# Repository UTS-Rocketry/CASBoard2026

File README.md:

# CAS Interface Board 2026

Control Actuation System (CAS) Interface Board for the UTS Rocketry avionics stack.

This board provides closed-loop control for the airbrake and roll control systems, along with sensor interfaces and onboard data logging. The design is based on the STM32F405RGT6 microcontroller and integrates inertial sensing, actuator control, and non-volatile storage.

The CAS board is intended to operate as part of the UTS Rocketry flight avionics architecture.

---

## Overview

The CAS Interface Board is responsible for:

- Airbrake deployment control
- Roll stabilization control
- Sensor acquisition
- Data logging
- Actuator interfacing

Closed-loop control is performed onboard using IMU and barometric sensor measurements.

---

## Hardware

### Microcontroller

STM32F405RGT6

- ARM Cortex-M4F
- 168 MHz
- Hardware floating point
- 1 MB Flash
- 192 KB RAM

---

### Sensors

#### IMU

LSM6DS3TR-C

Interface:

- SPI (4-wire)

Signals:

- SCK
- MOSI
- MISO
- CS
- DRDY Interrupt

Power:

- 3.3 V

---

#### Barometer

Interface:

- I2C

Signals:

- SCL
- SDA

Power:

- 3.3 V

---

### Storage

#### MicroSD Card

Interface:

- SPI

Signals:

- SCK
- MOSI
- MISO
- CS

Purpose:

- Flight data logging

---

#### External Flash

Interface:

- SPI

Purpose:

- Backup logging
- Blackbox storage

---

### Actuator Interfaces

#### Servo Outputs

- Airbrake Servo
- Roll Control Servo

Control Method:

- Timer PWM outputs

Power:

- Dedicated 5 V servo rail

Signal Voltage:

- 3.3 V logic

---

### Analog Inputs

#### Airbrake Position Feedback

External potentiometer input.

Signals:

- 3.3 V
- ADC Input
- GND

---

### Digital Inputs

#### Limit Switches

Digital inputs for actuator limits.

Typical configuration:

- External pull-down resistors
- GPIO input

---

#### IMU Interrupt

IMU data-ready interrupt.

Connected to STM32 EXTI input.

---

### Debug Interface

Serial Wire Debug (SWD)

Signals:

- SWDIO
- SWCLK
- NRST
- 3.3 V
- GND

Used for:

- Programming
- Debugging

---

## Communication Interfaces

### SPI Buses

SPI1

Used for:

- IMU

SPI2

Used for:

- MicroSD card
- External flash

---

### I2C Bus

I2C1

Used for:

- Barometer

---

## Power Architecture

### 3.3 V Rail

Supplies:

- MCU
- IMU
- Barometer
- Flash
- SD card logic

---

### 5 V Rail

Supplies:

- Servo motors

---

### Grounding

- Continuous ground plane
- Shared logic and servo ground

---

## Control System

### Airbrake Control

The CAS system predicts apogee using altitude and velocity estimates derived from sensor measurements.

Airbrake deployment is adjusted to reach the target apogee.

Inputs:

- Barometer altitude
- Estimated vertical velocity

Outputs:

- Airbrake servo PWM

---

### Roll Control

Roll stabilization is performed using gyroscope measurements from the IMU.

Inputs:

- Roll rate from IMU

Outputs:

- Roll control servo PWM

---

## Firmware

Development tools:

- STM32CubeMX
- STM32CubeIDE
- ST-Link

Features:

- SPI IMU driver
- I2C barometer driver
- PWM servo control
- SD card logging
- Flash logging
- Interrupt-driven sensor acquisition

---

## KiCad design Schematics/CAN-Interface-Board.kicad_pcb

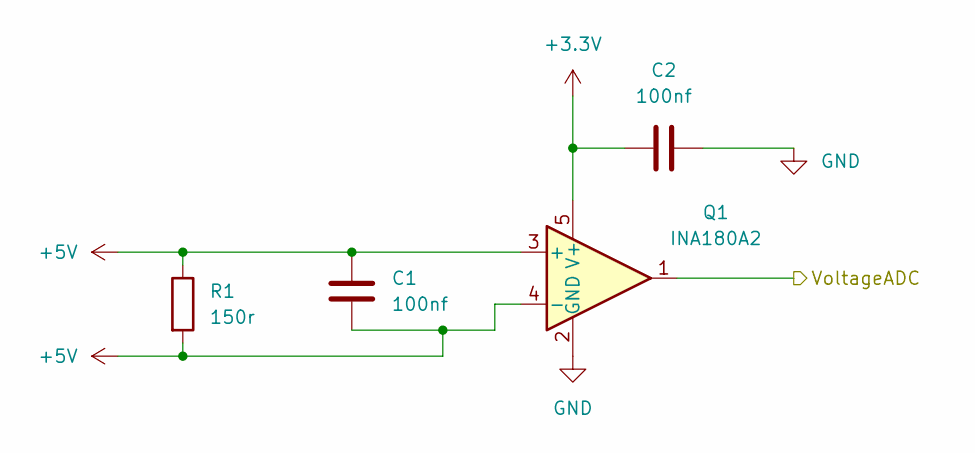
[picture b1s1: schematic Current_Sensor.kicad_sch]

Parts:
C1, C2: 100nf; C_0805_2012Metric_Pad1.18x1.45mm_HandSolder; LCSC Part C49678
Q1: INA180A2; SOT-23-5; LCSC Part C192764
R1: 150r; R_0805_2012Metric_Pad1.20x1.40mm_HandSolder; LCSC Part C4293416

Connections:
+3.3V: C2.1, Q1.5 (V+); also elsewhere on the board
+5V: C1.1, C1.2, Q1.3 (+), Q1.4 (-), R1.1, R1.2; also elsewhere on the board
/Current Sensor/VoltageADC: Q1.1; also elsewhere on the board
GND: C2.2, Q1.2 (GND); also elsewhere on the board

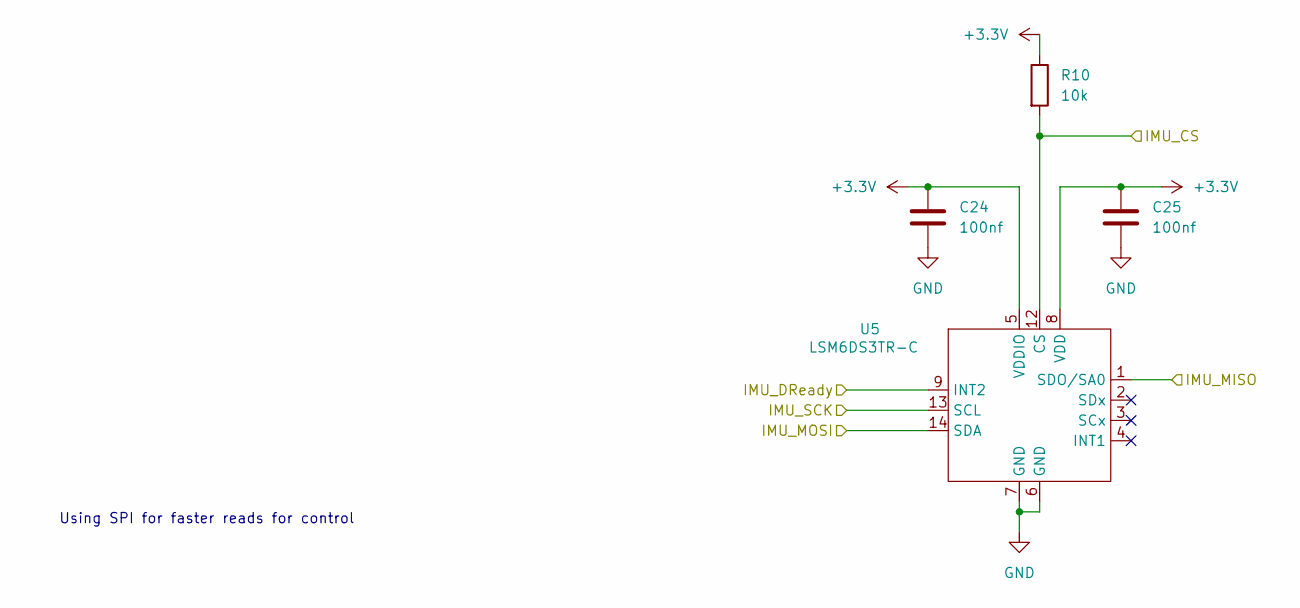
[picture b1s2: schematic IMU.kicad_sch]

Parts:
C24, C25: 100nf; C_0805_2012Metric_Pad1.18x1.45mm_HandSolder; LCSC Part C49678
R10: 10k; R_0805_2012Metric_Pad1.20x1.40mm_HandSolder; LCSC C84376
U5: LSM6DS3TR-C; LGA-14-2.5X3MM; LCSC Part C967633

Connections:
+3.3V: C24.1, C25.1, R10.1, U5.5 (VDDIO), U5.8 (VDD); also elsewhere on the board
/IMU/IMU_CS: R10.2, U5.12 (CS); also elsewhere on the board
/IMU/IMU_DReady: U5.9 (INT2); also elsewhere on the board
/IMU/IMU_MISO: U5.1 (SDO/SA0); also elsewhere on the board
/IMU/IMU_MOSI: U5.14 (SDA); also elsewhere on the board
/IMU/IMU_SCK: U5.13 (SCL); also elsewhere on the board
GND: C24.2, C25.2, U5.6 (GND), U5.7 (GND); also elsewhere on the board

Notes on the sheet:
Using SPI for faster reads for control

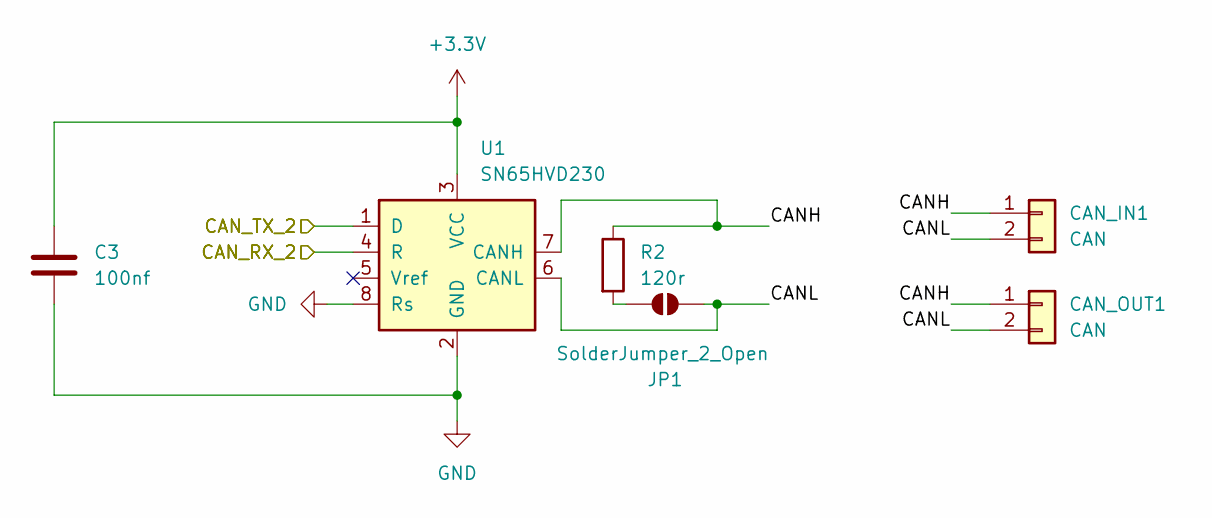
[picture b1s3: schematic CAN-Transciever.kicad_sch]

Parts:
C3: 100nf; C_0805_2012Metric_Pad1.18x1.45mm_HandSolder; LCSC Part C49678
CAN_IN1: CAN; MOLEX_26013114; LCSC Part C17644051
CAN_OUT1: CAN; MOLEX_26013114; LCSC Part C17644051
JP1: SolderJumper_2_Open; SolderJumper-2_P1.3mm_Open_TrianglePad1.0x1.5mm
R2: 120r; R_0805_2012Metric_Pad1.20x1.40mm_HandSolder; LCSC Part C269726
U1: SN65HVD230; SOIC-8_3.9x4.9mm_P1.27mm; LCSC Part C1543812

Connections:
+3.3V: C3.1, U1.3 (VCC); also elsewhere on the board
/CAN Transciever/CANH: CAN_IN1.1, CAN_OUT1.1, R2.1, U1.7 (CANH)
/CAN Transciever/CANL: CAN_IN1.2, CAN_OUT1.2, JP1.2 (B), U1.6 (CANL)
/CAN Transciever/CAN_RX_2: U1.4 (R); also elsewhere on the board
/CAN Transciever/CAN_TX_2: U1.1 (D); also elsewhere on the board
GND: C3.2, U1.2 (GND), U1.8 (Rs); also elsewhere on the board
unnamed: JP1.1 (A), R2.2

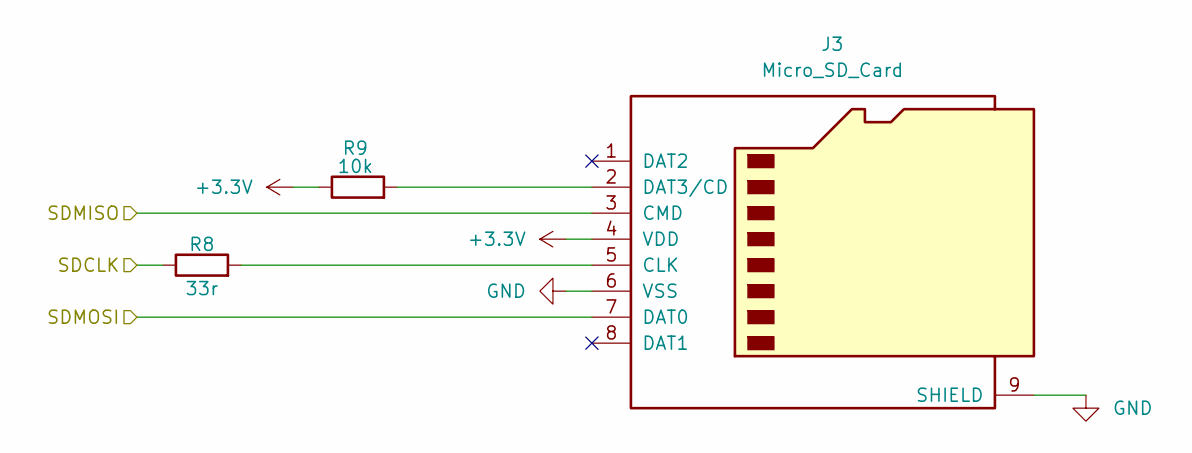
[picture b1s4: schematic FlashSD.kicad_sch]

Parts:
J3: Micro_SD_Card; microSD_HC_Molex_104031-0811; LCSC Part C164170
R8: 33r; R_0805_2012Metric_Pad1.20x1.40mm_HandSolder; LCSC Part C17557
R9: 10k; R_0805_2012Metric_Pad1.20x1.40mm_HandSolder; LCSC Part C84376

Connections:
+3.3V: J3.4 (VDD), R9.1; also elsewhere on the board
/FlashSD/SDCLK: R8.1; also elsewhere on the board
/FlashSD/SDMISO: J3.3 (CMD); also elsewhere on the board
/FlashSD/SDMOSI: J3.7 (DAT0); also elsewhere on the board
GND: J3.6 (VSS), J3.9 (SHIELD); also elsewhere on the board
unnamed: J3.5 (CLK), R8.2
unnamed: J3.2 (DAT3/CD), R9.2

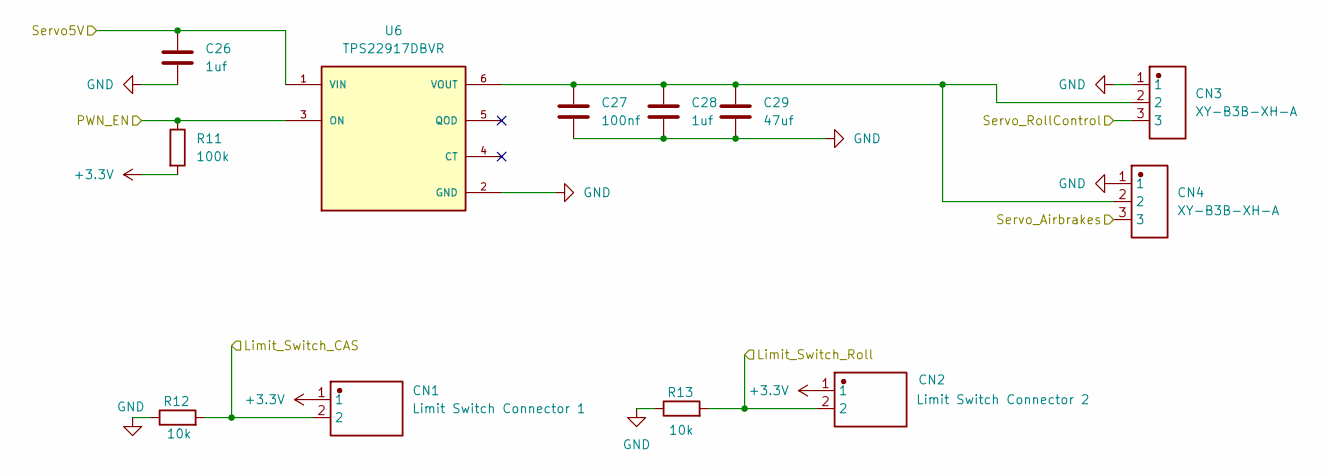
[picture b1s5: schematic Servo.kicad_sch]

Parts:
C26, C28: 1uf; C_0805_2012Metric_Pad1.18x1.45mm_HandSolder; LCSC C28323
C27: 100nf; C_0805_2012Metric_Pad1.18x1.45mm_HandSolder; LCSC C49678
C29: 47uf; C_0805_2012Metric_Pad1.18x1.45mm_HandSolder; LCSC C16780
CN1: Limit Switch Connector 1; JST_B2B-XH-A_LF__SN_; LCSC Part C158012
CN2: Limit Switch Connector 2; JST_B2B-XH-A_LF__SN_; LCSC Part C158012
CN3, CN4: XY-B3B-XH-A; JST_B3B-XH-A; LCSC Part C51940188
R11: 100k; R_0805_2012Metric_Pad1.20x1.40mm_HandSolder; LCSC C96346
R12, R13: 10k; R_0805_2012Metric_Pad1.20x1.40mm_HandSolder; LCSC Part C4277843
U6: TPS22917DBVR; SOT95P280X145-6N; LCSC C2681320

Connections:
+3.3V: CN1.1, CN2.1, R11.2; also elsewhere on the board
+5V: C26.1, U6.1 (VIN); also elsewhere on the board
/MCU/5Venable: R11.1, U6.3 (ON); also elsewhere on the board
/MCU/LimitSwitchCAS: CN1.2, R12.2; also elsewhere on the board
/MCU/LimitSwitchRoll: CN2.2, R13.2; also elsewhere on the board
/MCU/PWMServo_CAS: CN4.3; also elsewhere on the board
/MCU/PWMServo_Roll: CN3.3; also elsewhere on the board
/Servo/<NO NET>: C27.1, C28.1, C29.1, CN3.2, CN4.2, U6.6 (VOUT)
GND: C26.2, C27.2, C28.2, C29.2, CN3.1, CN4.1, R12.1, R13.1, U6.2 (GND); also elsewhere on the board

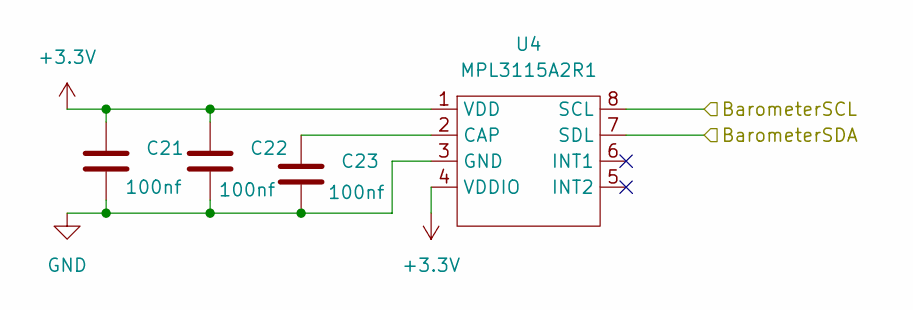
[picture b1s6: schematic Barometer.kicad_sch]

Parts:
C21, C22, C23: 100nf; C_0805_2012Metric_Pad1.18x1.45mm_HandSolder; LCSC Part C49678
U4: MPL3115A2R1; PSON80P300X300X100-8N; LCSC Part C54429

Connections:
+3.3V: C21.1, C22.1, U4.1 (VDD), U4.4 (VDDIO); also elsewhere on the board
/Barometer/BarometerSCL: U4.8 (SCL); also elsewhere on the board
/Barometer/BarometerSDA: U4.7 (SDL); also elsewhere on the board
GND: C21.2, C22.2, C23.2, U4.3 (GND); also elsewhere on the board
unnamed: C23.1, U4.2 (CAP)

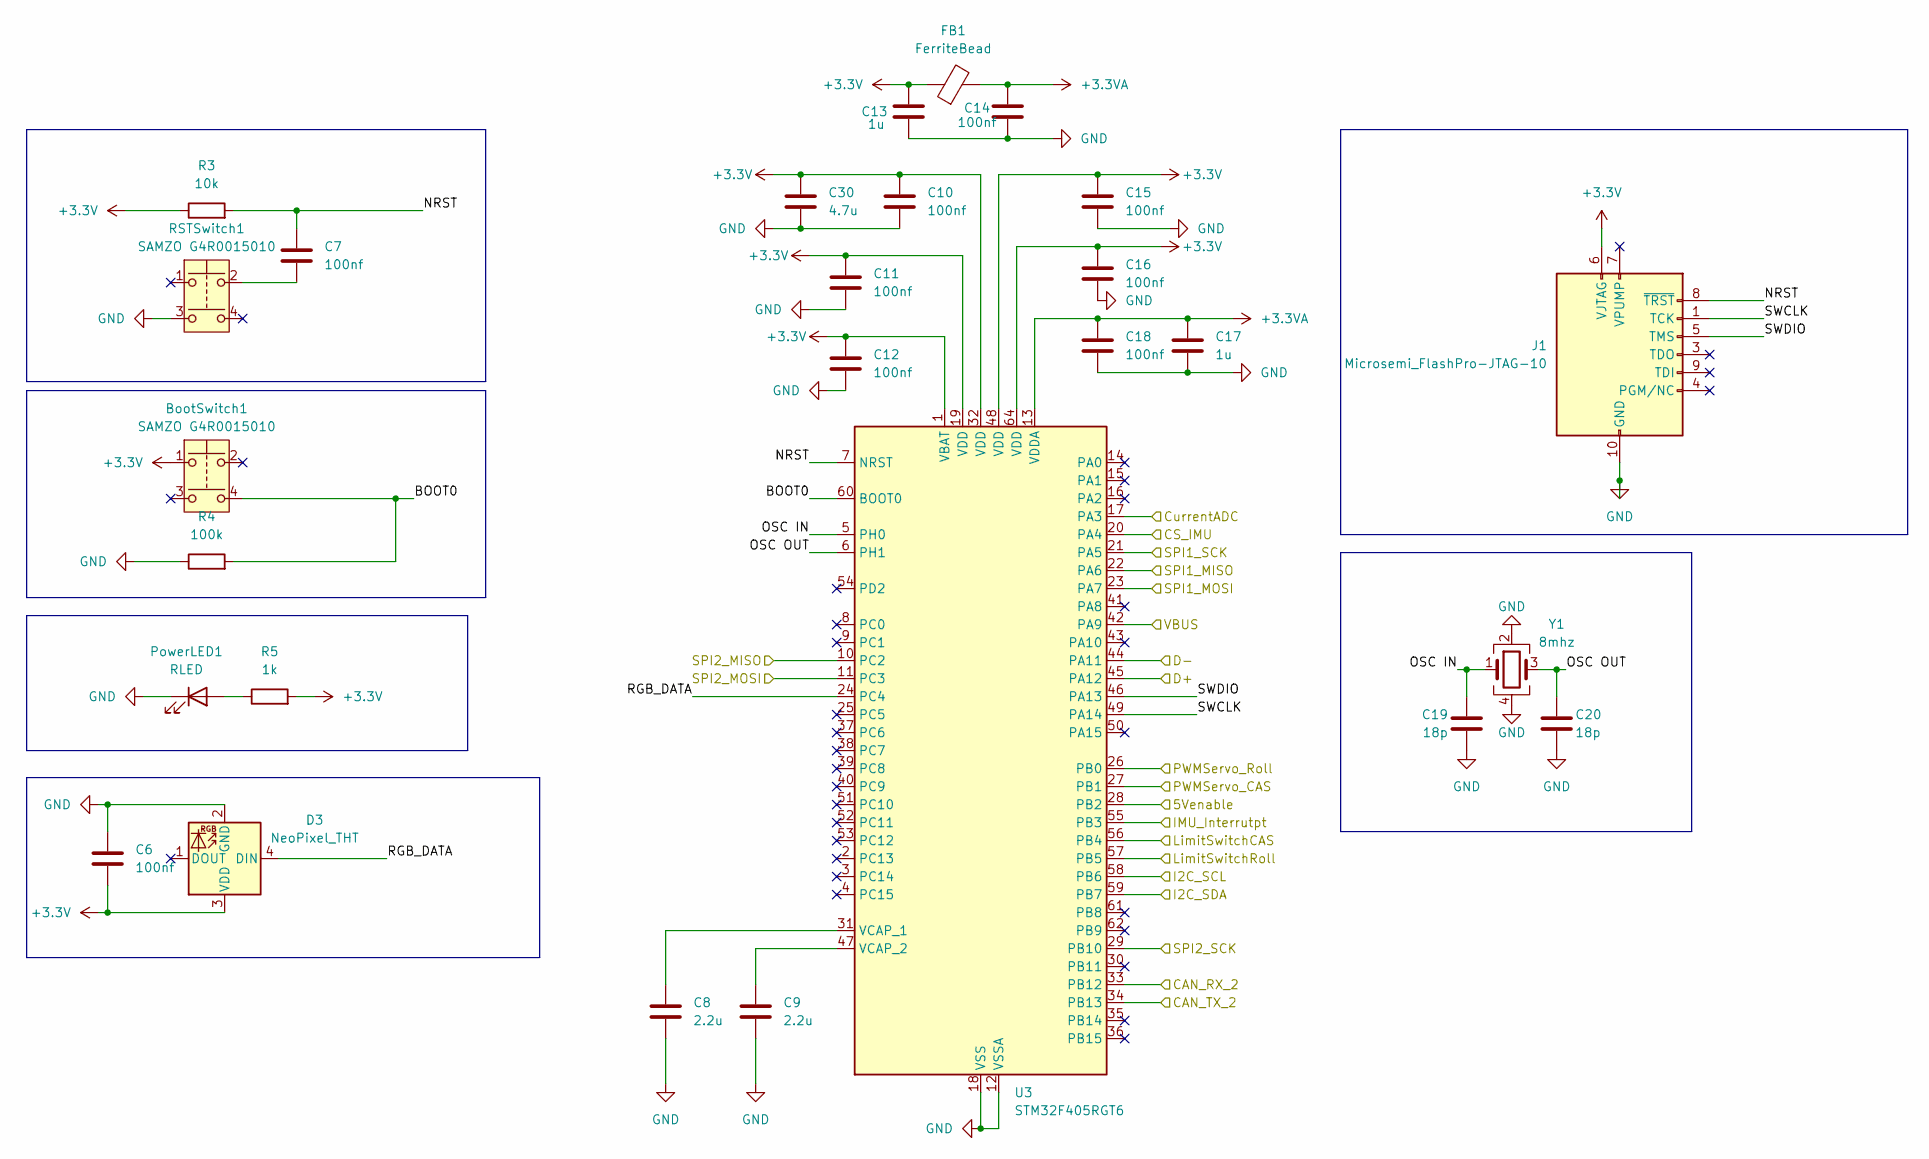
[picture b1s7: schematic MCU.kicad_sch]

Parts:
BootSwitch1: SAMZO G4R0015010; LCSC Part C49393646
C6, C7: 100nf; C_0805_2012Metric_Pad1.18x1.45mm_HandSolder; LCSC Part C49678
C8, C9: 2.2u; C_0805_2012Metric_Pad1.18x1.45mm_HandSolder; LCSC C19110
C10, C11, C12, C14, C15, C16, C18: 100nf; C_0805_2012Metric_Pad1.18x1.45mm_HandSolder; LCSC C49678
C13, C17: 1u; C_0805_2012Metric_Pad1.18x1.45mm_HandSolder; LCSC C28323
C19, C20: 18p; C_0805_2012Metric_Pad1.18x1.45mm_HandSolder; LCSC Part C170109
C30: 4.7u; C_0805_2012Metric_Pad1.18x1.45mm_HandSolder
D3: NeoPixel_THT; LED_Kingbright_AAA3528ESGCT; LCSC Part C2827321
FB1: FerriteBead; R_0805_2012Metric_Pad1.20x1.40mm_HandSolder; LCSC C85840
J1: Microsemi_FlashPro-JTAG-10; CONN_7024610XX_MOL; LCSC Part C585350
PowerLED1: RLED; LED_0603_1608Metric_Pad1.05x0.95mm_HandSolder; LCSC Part C965799
R3: 10k; R_0805_2012Metric_Pad1.20x1.40mm_HandSolder; LCSC Part C84376
R4: 100k; R_0805_2012Metric_Pad1.20x1.40mm_HandSolder; LCSC Part C96346
R5: 1k; R_0805_2012Metric_Pad1.20x1.40mm_HandSolder; LCSC Part C95781
RSTSwitch1: SAMZO G4R0015010; LCSC Part C49393646
U3: STM32F405RGT6; LQFP-64_10x10mm_P0.5mm; LCSC C15742
Y1: 8mhz; Crystal_SMD_3225-4Pin_3.2x2.5mm_HandSoldering; LCSC Part C19723344

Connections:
+3.3V: BootSwitch1.1, C6.2, C10.1, C11.1, C12.1, C13.2, C15.1, C16.1, C30.1, D3.3 (VDD), FB1.1, J1.6 (VJTAG), R3.1, R5.2, U3.1 (VBAT), U3.19 (VDD), U3.32 (VDD), U3.48 (VDD), U3.64 (VDD); also elsewhere on the board
+3.3VA: C14.2, C17.1, C18.1, FB1.2, U3.13 (VDDA)
/Barometer/BarometerSCL: U3.58 (PB6); also elsewhere on the board
/Barometer/BarometerSDA: U3.59 (PB7); also elsewhere on the board
/CAN Transciever/CAN_RX_2: U3.34 (PB13); also elsewhere on the board
/CAN Transciever/CAN_TX_2: U3.33 (PB12); also elsewhere on the board
/Current Sensor/VoltageADC: U3.17 (PA3); also elsewhere on the board
/FlashSD/SDCLK: U3.29 (PB10); also elsewhere on the board
/FlashSD/SDMISO: U3.10 (PC2); also elsewhere on the board
/FlashSD/SDMOSI: U3.11 (PC3); also elsewhere on the board
/IMU/IMU_CS: U3.20 (PA4); also elsewhere on the board
/IMU/IMU_DReady: U3.55 (PB3); also elsewhere on the board
/IMU/IMU_MISO: U3.22 (PA6); also elsewhere on the board
/IMU/IMU_MOSI: U3.23 (PA7); also elsewhere on the board
/IMU/IMU_SCK: U3.21 (PA5); also elsewhere on the board
/MCU/5Venable: U3.28 (PB2); also elsewhere on the board
/MCU/BOOT0: BootSwitch1.4, R4.2, U3.60 (BOOT0)
/MCU/D+: U3.45 (PA12); also elsewhere on the board
/MCU/D-: U3.44 (PA11); also elsewhere on the board
/MCU/LimitSwitchCAS: U3.56 (PB4); also elsewhere on the board
/MCU/LimitSwitchRoll: U3.57 (PB5); also elsewhere on the board
/MCU/NRST: C7.1, J1.8 (~TRST), R3.2, U3.7 (NRST)
/MCU/OSC IN: C19.1, U3.5 (PH0), Y1.1
/MCU/OSC OUT: C20.1, U3.6 (PH1), Y1.3
/MCU/PWMServo_CAS: U3.27 (PB1); also elsewhere on the board
/MCU/PWMServo_Roll: U3.26 (PB0); also elsewhere on the board
/MCU/RGB_DATA: D3.4 (DIN), U3.24 (PC4)
/MCU/SWCLK: J1.1 (TCK), U3.49 (PA14)
/MCU/SWDIO: J1.5 (TMS), U3.46 (PA13)
/USB5V: U3.42 (PA9); also elsewhere on the board
GND: C6.1, C8.2, C9.2, C10.2, C11.2, C12.2, C13.1, C14.1, C15.2, C16.2, C17.2, C18.2, C19.2, C20.2, C30.2, D3.2 (GND), J1.2 (GND), J1.10 (GND), PowerLED1.1 (K), R4.1, RSTSwitch1.3, U3.12 (VSSA), U3.18 (VSS), U3.63 (VSS), Y1.2, Y1.4; also elsewhere on the board
unnamed: C7.2, RSTSwitch1.2
unnamed: PowerLED1.2 (A), R5.1
unnamed: C8.1, U3.31 (VCAP_1)
unnamed: C9.1, U3.47 (VCAP_2)

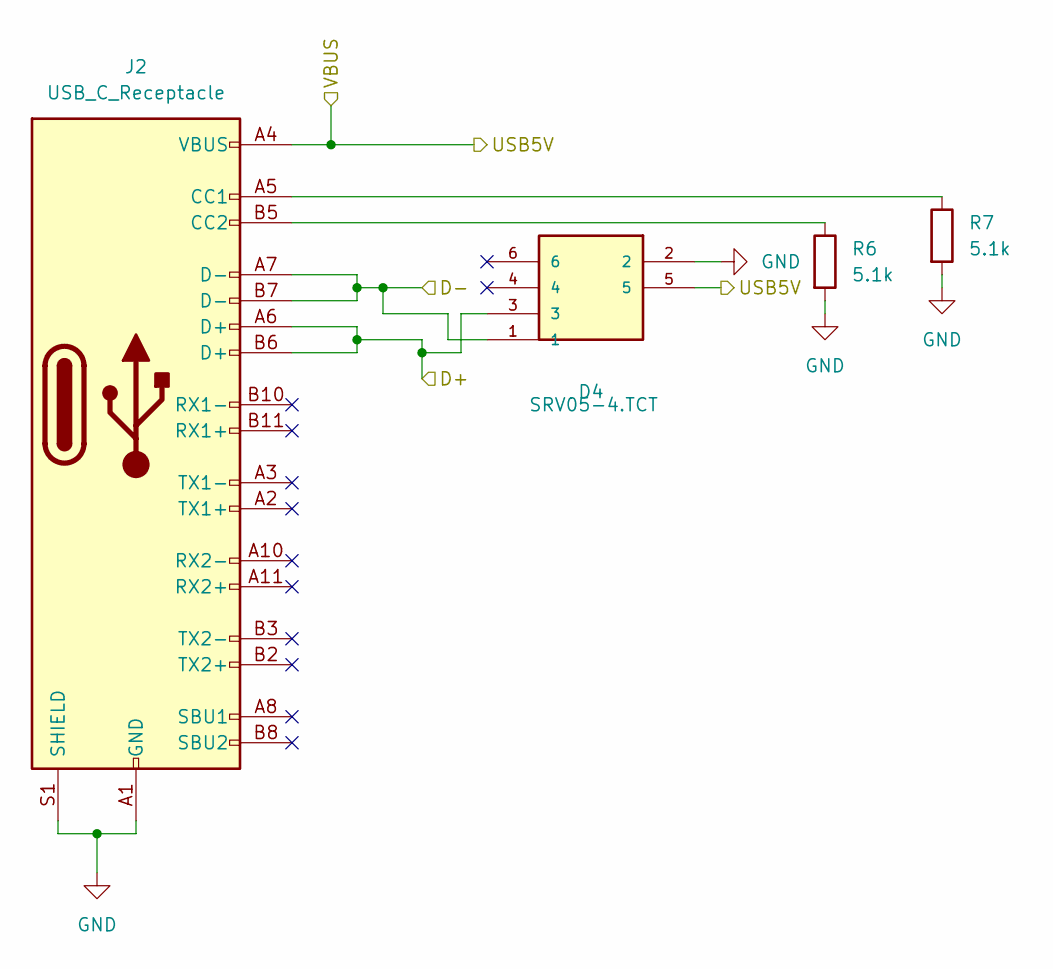
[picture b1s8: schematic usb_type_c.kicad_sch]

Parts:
D4: SRV05-4.TCT; SOT-23-6_L2.9-W1.6-P0.95-LS2.8-BR; MOUSER_PART_NUMBER 947-SRV05-4.TCT
J2: USB_C_Receptacle; USB_C_Receptacle_HRO_TYPE-C-31-M-12; LCSC C49566391
R6, R7: 5.1k; R_0805_2012Metric_Pad1.20x1.40mm_HandSolder; LCSC C27834

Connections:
/MCU/D+: D4.3, J2.A6 (D+), J2.B6 (D+); also elsewhere on the board
/MCU/D-: D4.1, J2.A7 (D-), J2.B7 (D-); also elsewhere on the board
/USB5V: D4.5, J2.A4 (VBUS), J2.A9 (VBUS), J2.B4 (VBUS), J2.B9 (VBUS); also elsewhere on the board
GND: D4.2, J2.A1 (GND), J2.A12 (GND), J2.B1 (GND), J2.B12 (GND), J2.S1 (SHIELD), R6.2, R7.2; also elsewhere on the board
unnamed: J2.A5 (CC1), R7.1
unnamed: J2.B5 (CC2), R6.1

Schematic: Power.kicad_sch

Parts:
C4: 1u; C_0805_2012Metric_Pad1.18x1.45mm_HandSolder; LCSC Part C28323
C5: 4.7u; C_0805_2012Metric_Pad1.18x1.45mm_HandSolder; LCSC Part C98192
D1, D2: D_Schottky; D_2114_3652Metric; LCSC C113936
J_BUCK_IN_A1: PinSocket_1x02_P2.54mm_Horizontal
J_BUCK_IN_B1: PinSocket_1x02_P2.54mm_Horizontal
J_BUCK_OUT_A1: PinSocket_1x02_P2.54mm_Horizontal
J_BUCK_OUT_B1: PinSocket_1x02_P2.54mm_Horizontal
PowerIn1: 2 pin Molex; MOLEX_26013114; LCSC C17644051
U2: LDL1117-3.3; SOT230P700X180-4N; LCSC C435835

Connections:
+3.3V: C5.1, U2.3 (Vout), U2.4 (Vout); also elsewhere on the board
+5V: J_BUCK_OUT_B1.1, J_BUCK_OUT_B1.2; also elsewhere on the board
+BATT: D1.2 (A), J_BUCK_IN_B1.1, J_BUCK_IN_B1.2, PowerIn1.1
/USB5V: D2.2 (A); also elsewhere on the board
GND: C4.2, C5.2, J_BUCK_IN_A1.1, J_BUCK_IN_A1.2, J_BUCK_OUT_A1.1, J_BUCK_OUT_A1.2, PowerIn1.2, U2.2 (GND); also elsewhere on the board
unnamed: C4.1, D1.1 (K), D2.1 (K), U2.1 (Vin)

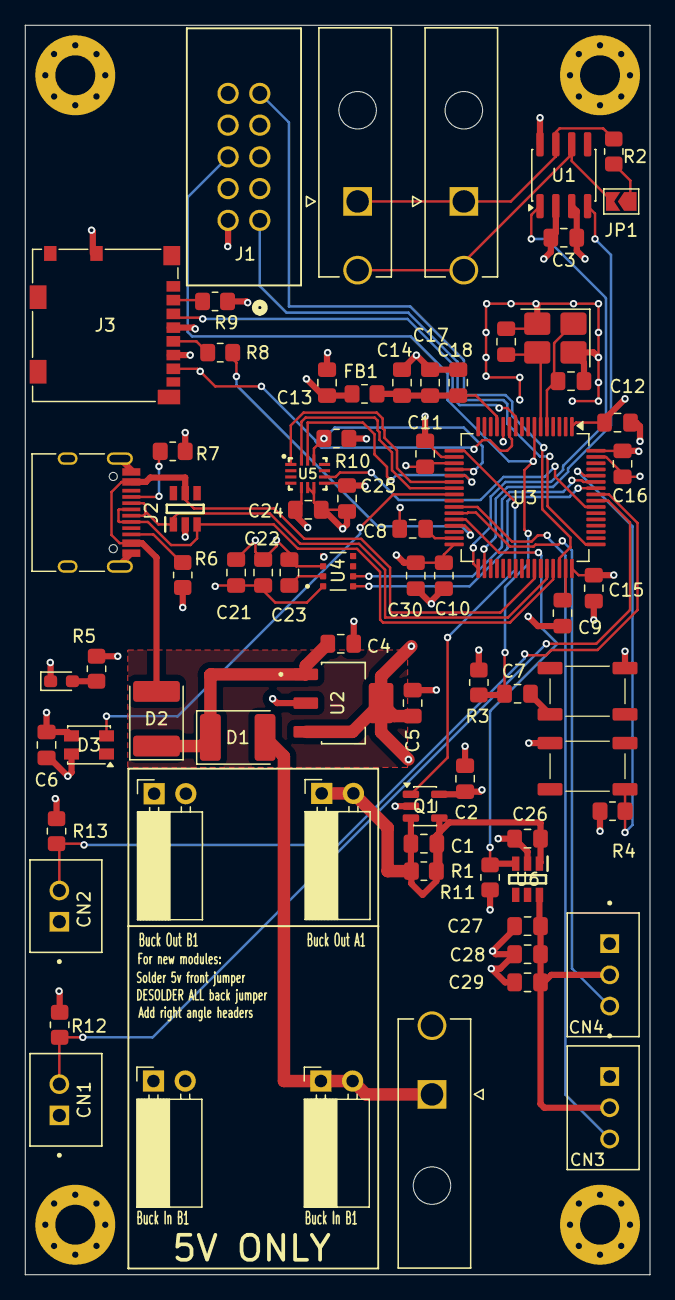
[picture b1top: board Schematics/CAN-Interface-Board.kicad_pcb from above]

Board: 4 copper layers, 50.0 x 100.0 mm, 74 parts (0 on the bottom side), 47 nets.

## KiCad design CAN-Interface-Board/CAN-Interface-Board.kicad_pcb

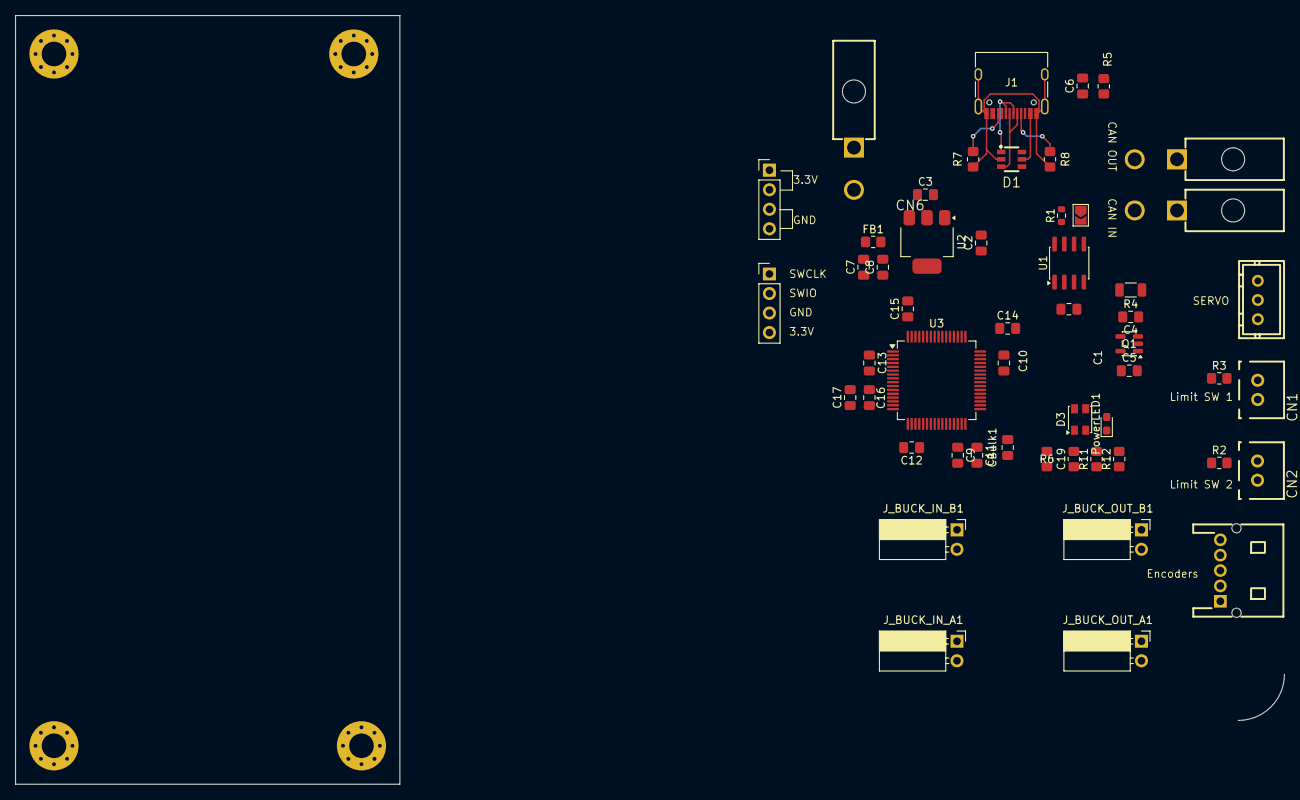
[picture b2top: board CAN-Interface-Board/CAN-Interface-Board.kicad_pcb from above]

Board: 4 copper layers, 165.1 x 100.0 mm, 52 parts (0 on the bottom side), 31 nets.

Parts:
C1, C2, C4, C5: 100nF; C_0805_2012Metric_Pad1.18x1.45mm_HandSolder
C3: 10uF; C_0805_2012Metric_Pad1.18x1.45mm_HandSolder
C6, C8, C11, C12, C13, C14, C15, C17: 100nf; C_0805_2012Metric_Pad1.18x1.45mm_HandSolder
C7, C16: 1u; C_0805_2012Metric_Pad1.18x1.45mm_HandSolder
C9, C10: 2.2u; C_0805_2012Metric_Pad1.18x1.45mm_HandSolder
C19: 100nf; R_0805_2012Metric_Pad1.20x1.40mm_HandSolder
CBulk1: 4.7u; C_0805_2012Metric_Pad1.18x1.45mm_HandSolder
CN1: Limit Switch Connector 1; JST B2B-XH-A(LF)(SN)
CN2: Limit Switch Connector 2; JST B2B-XH-A(LF)(SN)
CN3: Encoder Connector; CONN-TH_S05B-PASK-2-LF-SN
CN5: XY-B3B-XH-A; CONN-TH_3P-P2.50_A2501WV2-3P
CN6: MOLEX_26013114; MOLEX 26013114
CN7: MOLEX_CAN_IN; MOLEX 26013114
CN8: MOLEX_CAN_OUT; MOLEX 26013114
D1: SRV05-4.TCT; SOT-23-6_L2.9-W1.6-P0.95-LS2.8-BR
D3: NeoPixel_THT; LED_Kingbright_AAA3528ESGCT
FB1: FerriteBead; R_0805_2012Metric_Pad1.20x1.40mm_HandSolder
J1: USB_C_Receptacle; USB_C_Receptacle_HRO_TYPE-C-31-M-12
J2, J4: Conn_01x04_Pin; PinHeader_1x04_P2.54mm_Vertical
JP1: SolderJumper_2_Open; SolderJumper-2_P1.3mm_Open_TrianglePad1.0x1.5mm
J_BUCK_IN_A1: PinSocket_1x02_P2.54mm_Horizontal
J_BUCK_IN_B1: PinSocket_1x02_P2.54mm_Horizontal
J_BUCK_OUT_A1: PinSocket_1x02_P2.54mm_Horizontal
J_BUCK_OUT_B1: PinSocket_1x02_P2.54mm_Horizontal
PowerLED1: RLED; LED_0603_1608Metric_Pad1.05x0.95mm_HandSolder
Q1: INA180A2; SOT-23-5
R1: 120R; R_0603_1608Metric
R2, R3: 10K; R_0805_2012Metric_Pad1.20x1.40mm_HandSolder
R4: 0.015Ohm; R_1206_3216Metric
R5: 10k; R_0805_2012Metric_Pad1.20x1.40mm_HandSolder
R6: 100k; R_0805_2012Metric_Pad1.20x1.40mm_HandSolder
R7, R8: 5.1k; R_0805_2012Metric_Pad1.20x1.40mm_HandSolder
R11: 1k; R_0805_2012Metric_Pad1.20x1.40mm_HandSolder
R12: .33k; R_0805_2012Metric_Pad1.20x1.40mm_HandSolder
U1: SN65HVD230; SOIC-8_3.9x4.9mm_P1.27mm
U2: LD1117S33TR; SOT-223-3_TabPin2
U3: STM32F405RGTx; LQFP-64_10x10mm_P0.5mm

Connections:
+3.3V: C1.1, C2.1, C5.1, C7.2, C8.2, C11.1, C12.1, C13.1, C14.1, C15.1, C16.1, C17.1, CBulk1.1, CN1.1, CN2.1, CN3.1, FB1.1, FB1.2, J2.1, J2.2, J4.4, Q1.5 (V+), R5.1, R11.2, U1.3 (VCC), U2.2 (VO), U3.1 (VBAT), U3.13 (VDDA), U3.19 (VDD), U3.32 (VDD), U3.48 (VDD), U3.64 (VDD)
+5V: C4.1, C19.2, D1.5, D3.3 (VDD), J1.A4 (VBUS), J1.A9 (VBUS), J1.B4 (VBUS), J1.B9 (VBUS), J_BUCK_OUT_A1.1, J_BUCK_OUT_B1.1, Q1.3 (+), R4.1, U3.43 (PA10)
/CANH: CN7.1, CN8.1, R1.1, U1.7 (CANH)
/CANL: CN7.2, CN8.2, JP1.2 (B), U1.6 (CANL)
/MCU/BOOT0: R6.2, U3.60 (BOOT0)
/MCU/D+: D1.1, J1.A6 (D+), J1.B6 (D+), U3.45 (PA12)
/MCU/D-: D1.3, J1.A7 (D-), J1.B7 (D-), U3.44 (PA11)
/MCU/NRST: C6.1, R5.2, U3.7 (NRST)
/MCU/RGB_DATA: R12.2, U3.24 (PC4)
/MCU/SWCLK: J4.1, U3.49 (PA14)
/MCU/SWDIO: J4.2, U3.46 (PA13)
/VBAT: J_BUCK_IN_A1.1, J_BUCK_IN_B1.1
CAN_D: U1.1 (D), U3.34 (PB13)
CAN_R: U1.4 (R), U3.33 (PB12)
CAN_RS: U1.8 (Rs), U3.21 (PA5)
Current_Sensor_Output: Q1.1, U3.17 (PA3)
ENCODER_A: CN3.3, U3.14 (PA0)
ENCODER_B: CN3.4, U3.15 (PA1)
GND: C1.2, C2.2, C3.2, C5.2, C7.1, C8.1, C9.2, C10.2, C11.2, C12.2, C13.2, C14.2, C15.2, C16.2, C17.2, C19.1, CBulk1.2, CN3.2, CN5.1, CN6.1, D1.2, D3.2 (GND), J1.A1 (GND), J1.A12 (GND), J1.B1 (GND), J1.B12 (GND), J1.S1 (SHIELD), J2.3, J2.4, J4.3, J_BUCK_IN_A1.2, J_BUCK_IN_B1.2, J_BUCK_OUT_A1.2, J_BUCK_OUT_B1.2, PowerLED1.1 (K), Q1.2 (GND), R2.1, R3.1, R6.1, R7.2, R8.2, U1.2 (GND), U2.1 (GND), U3.12 (VSSA), U3.18 (VSS), U3.63 (VSS)
Limit_Switch_A: CN1.2, R3.2
Limit_Switch_B: CN2.2, R2.2
unnamed: D3.4 (DIN), R12.1
unnamed: J1.A5 (CC1), R8.1
unnamed: J1.B5 (CC2), R7.1
unnamed: JP1.1 (A), R1.2
unnamed: PowerLED1.2 (A), R11.1
unnamed: C9.1, U3.31 (VCAP_1)
unnamed: C10.1, U3.47 (VCAP_2)
Servo_Signal: CN5.3, U3.23 (PA7)
Servo_VCC: C4.2, CN5.2, Q1.4 (-), R4.2
VCC: C3.1, CN6.2, U2.3 (VI)

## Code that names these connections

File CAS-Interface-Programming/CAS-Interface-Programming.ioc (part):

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Mcu.Name=STM32F405RGTx
Mcu.Package=LQFP64
Mcu.UserName=STM32F405RGTx
PA0-WKUP.Signal=ADCx_IN0
PA1.Signal=ADCx_IN1
PA13.Mode=Serial_Wire
PA13.Signal=SYS_JTMS-SWDIO
PA14.Mode=Serial_Wire
PA14.Signal=SYS_JTCK-SWCLK
PA3.Signal=ADCx_IN3
PA5.Signal=GPIO_Output
PA7.Signal=S_TIM14_CH1
PB12.Mode=CAN_Activate
PB12.Signal=CAN2_RX
PB13.Mode=CAN_Activate
PB13.Signal=CAN2_TX
PC4.Signal=GPIO_Output
RCC.HSE_VALUE=25000000
RCC.SYSCLKFreq_VALUE=16000000
board=custom

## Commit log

2026-02-04 altered connectors, layout refinement, added LEDS
2026-02-04 STM32IDE Project Added
2026-02-09 added gitignore to clean remote repo
2026-02-15 Began conversion for full CAS Control
2026-02-22 altered sensor schematics
2026-02-24 editing schematic
2026-02-24 removed gitstatus
2026-02-24 cleaned up repo
2026-02-25 finished and ERC schematic
2026-02-25 inital layout started, refining stage
2026-02-25 first round of routing complete need to pass DRC first and need to reroute more effiencently
2026-02-25 fixed schematic
2026-02-25 put note to fix nets on current sensor
